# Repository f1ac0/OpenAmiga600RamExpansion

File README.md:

# OpenAmiga600RamExpansion
OpenAmiga600RamExpansion is an Open Hardware 1 MB Chip RAM Expansion for the Commodore Amiga 600 Computer with optional Real Time Clock, by SukkoPera https://github.com/SukkoPera/OpenAmiga600RamExpansion/.

This project is a different layout of the board, with almost the same BOM :
- smaller board, no space for ram chips sockets,
- inverted connector, so that components are facing downside and the solder joints do not touch the trapdoor,
- footprint for CR1220 in addition to the CR2032.

# Disclaimer
This is a hobbyist project, it comes with no warranty and no support.

This version is not connected to SukkoPera, please don't bother him with issues you might have because of it.

I publish this work using the same license as the original project : CERN OHL v1.2.

If you find it useful, please reward the original author. See the original repository.

# Making it
You should refer to the original repository where SukkoPera provides excellent advice about connector availability, RAM chips to use (I personally installed V53C16256HK40) and RTC. I confirm that AmigaTestKit is a must to check that the board is working fine (among other test).

Check for shorts at least between 5V and GND traces before applying power !

# Using it
- Install the battery,
- Plug to the motherboard,
- Power on the system.

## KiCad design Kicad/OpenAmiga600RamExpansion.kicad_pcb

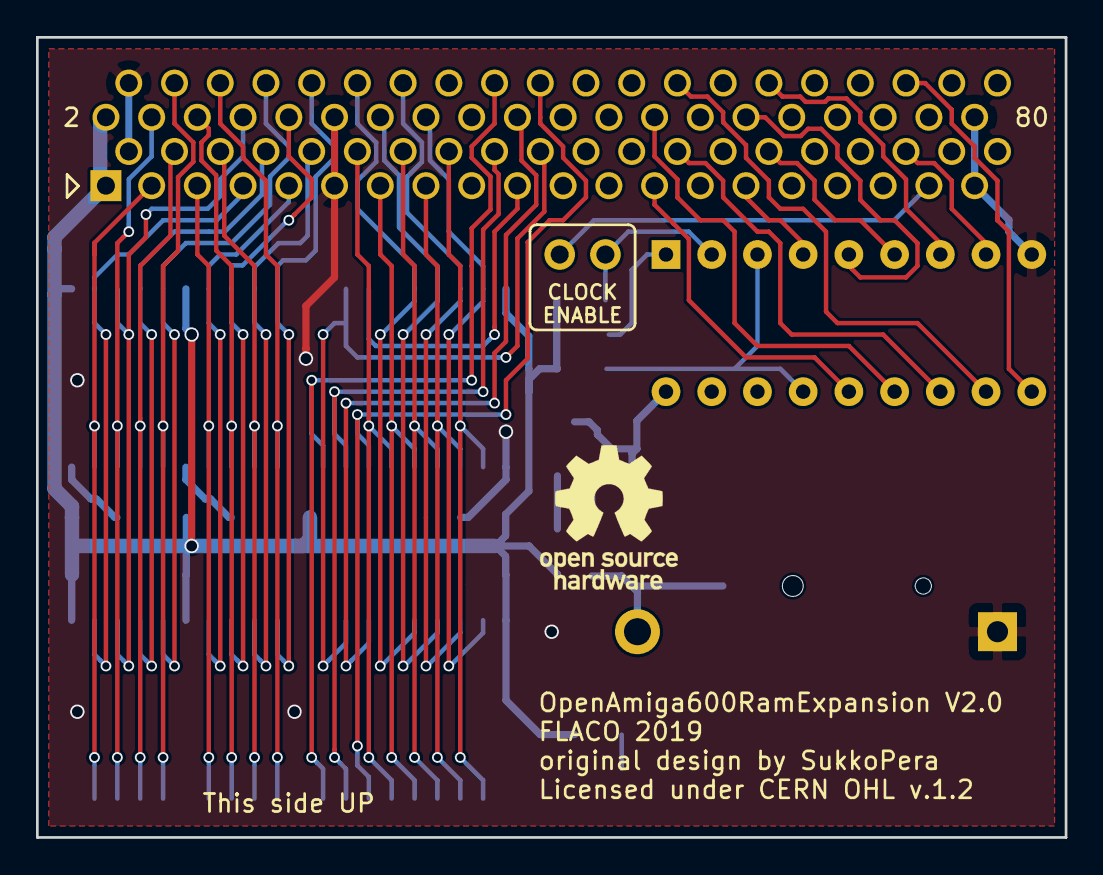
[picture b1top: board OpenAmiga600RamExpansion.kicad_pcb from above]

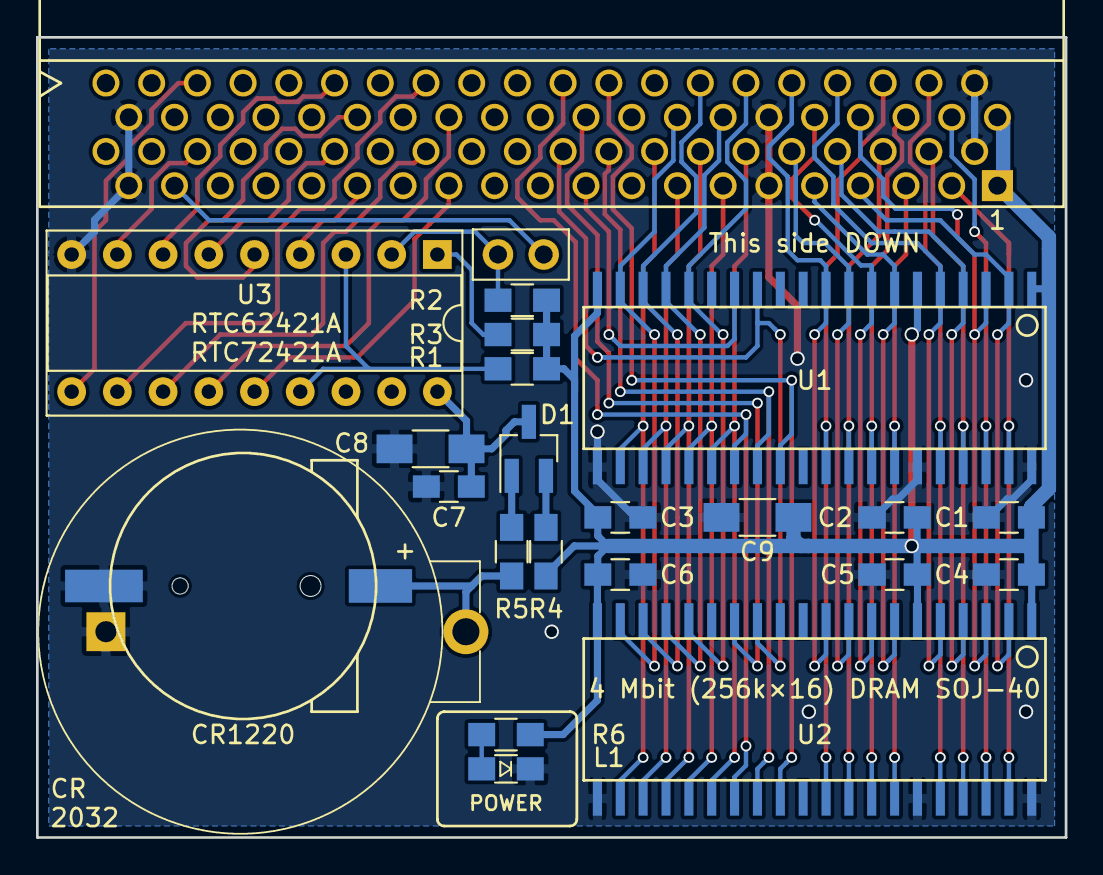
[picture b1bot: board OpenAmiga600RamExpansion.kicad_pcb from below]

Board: 2 copper layers, 57.2 x 44.4 mm, 25 parts (24 on the bottom side), 52 nets.

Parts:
BT1: CR2032; Battery_Holder_Coin_2032_BS-7
BT2: CR1220; Battery_Holder_Coin_1220_BS-1220-1
C1, C2, C3, C4, C5, C6, C7: 100n; C_0805_HandSoldering
C8: 2.2uF; C_1206_HandSoldering
C9: 10uF; C_1206_HandSoldering
CONN1: A600_TRAPDOOR; 4UCON_10156_90deg_A600
D1: BAT54C; SOT-23_Handsoldering
J1: Conn_01x02; Pin_Header_Straight_1x02-ModSilkS
J99: OSHW_LOGO; OSHW-Logo_7.5x8mm_SilkScreen
L1: LED; LED_0805_HandSoldering_ModSilkS
R1, R2, R3: 10k; R_0805_HandSoldering
R4, R5: 220; R_0805_HandSoldering
R6: 1K; R_0805_HandSoldering
U1, U2: NEC_424260; SOJ-40-longpads
U3: MSM6242B; DIP-18_W7.62mm_Socket

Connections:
/CASL1: CONN1.35, U1.28, U2.28
/CASU1: CONN1.36, U1.29, U2.29
/OE: CONN1.40, U1.27, U2.27
/RAS0: CONN1.37, U1.14
/RAS1: CONN1.38, U2.14
/WE: CONN1.39, U1.13, U2.13
/a0: CONN1.24, U1.16, U2.16
/a1: CONN1.26, U1.17, U2.17
/a2: CONN1.28, U1.18, U2.18
/a3: CONN1.30, U1.19, U2.19
/a4: CONN1.31, U1.22, U2.22
/a5: CONN1.29, U1.23, U2.23
/a6: CONN1.27, U1.24, U2.24
/a7: CONN1.25, U1.25, U2.25
/a8: CONN1.23, U1.26, U2.26
/d0: CONN1.13, U1.2, U2.2
/d1: CONN1.14, U1.3, U2.3
/d2: CONN1.15, U1.4, U2.4
/d3: CONN1.16, U1.5, U2.5
/d4: CONN1.17, U1.7, U2.7
/d5: CONN1.18, U1.8, U2.8
/d6: CONN1.19, U1.9, U2.9
/d7: CONN1.20, U1.10, U2.10
/d8: CONN1.12, U1.31, U2.31
/d9: CONN1.11, U1.32, U2.32
/d10: CONN1.10, U1.33, U2.33
/d11: CONN1.9, U1.34, U2.34
/d12: CONN1.8, U1.36, U2.36
/d13: CONN1.7, U1.37, U2.37
/d14: CONN1.6, U1.38, U2.38
/d15: CONN1.5, U1.39, U2.39
/rtc_a0: CONN1.57, U3.4
/rtc_a1: CONN1.58, U3.5
/rtc_a2: CONN1.59, U3.6
/rtc_a3: CONN1.60, U3.7
/rtc_cs: CONN1.73, J1.2
/rtc_d0: CONN1.49, U3.14
/rtc_d1: CONN1.50, U3.13
/rtc_d2: CONN1.51, U3.12
/rtc_d3: CONN1.52, U3.11
/rtc_rd: CONN1.71, U3.8
/rtc_wr: CONN1.72, U3.10
GND: BT1.2, BT2.2, C1.2, C2.2, C3.2, C4.2, C5.2, C6.2, C7.2, C8.2, C9.2, CONN1.3, CONN1.4, CONN1.21, CONN1.22, CONN1.77, CONN1.78, L1.1, U1.21, U1.35, U1.40, U2.21, U2.35, U2.40, U3.9
unnamed: BT1.1, BT2.1, R5.1
unnamed: D1.1, R5.2
unnamed: D1.2, R4.2
unnamed: J1.1, R2.2, U3.2
unnamed: L1.2, R6.1
unnamed: R1.2, U3.3, U3.15
unnamed: R3.2, U3.1
VCC: C1.1, C2.1, C3.1, C4.1, C5.1, C6.1, C9.1, CONN1.1, CONN1.2, R1.1, R2.1, R3.1, R4.1, R6.2, U1.1, U1.6, U1.20, U2.1, U2.6, U2.20
VDD: C7.1, C8.1, D1.3, U3.18

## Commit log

2020-09-08 Respository init with KiCAD files, Readme and License
2022-02-15 Photo and InteractiveHtmlBom

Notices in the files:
Kicad/OpenAmiga600RamExpansion.kicad_pcb:
Licensed under CERN OHL v.1.2
